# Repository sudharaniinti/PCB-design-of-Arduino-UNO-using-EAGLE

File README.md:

# PCB-design-of-Arduino-UNO-using-EAGLE
PCB (Printed Circuit Board) designing is the process of creating the layout and design of a printed circuit board used to connect electronic components. I designed my first PCB using EAGLE Software! I designed an Arduino UNO board with basic features, including a Microcontroller module, Power Module, and input/output pins. EAGLE is electronic design automation (EDA) software that lets printed circuit board (PCB) designers seamlessly connect schematic diagrams, component placement, PCB routing and comprehensive library content.  EAGLE stands for Easily Applicable Graphical Layout Editor 

This repository contains the following:

1. Eagle schematic file

2. Eagle board file

3. BOM(Bill of Materials)

4. Gerbers

5. PDFs of the schematic

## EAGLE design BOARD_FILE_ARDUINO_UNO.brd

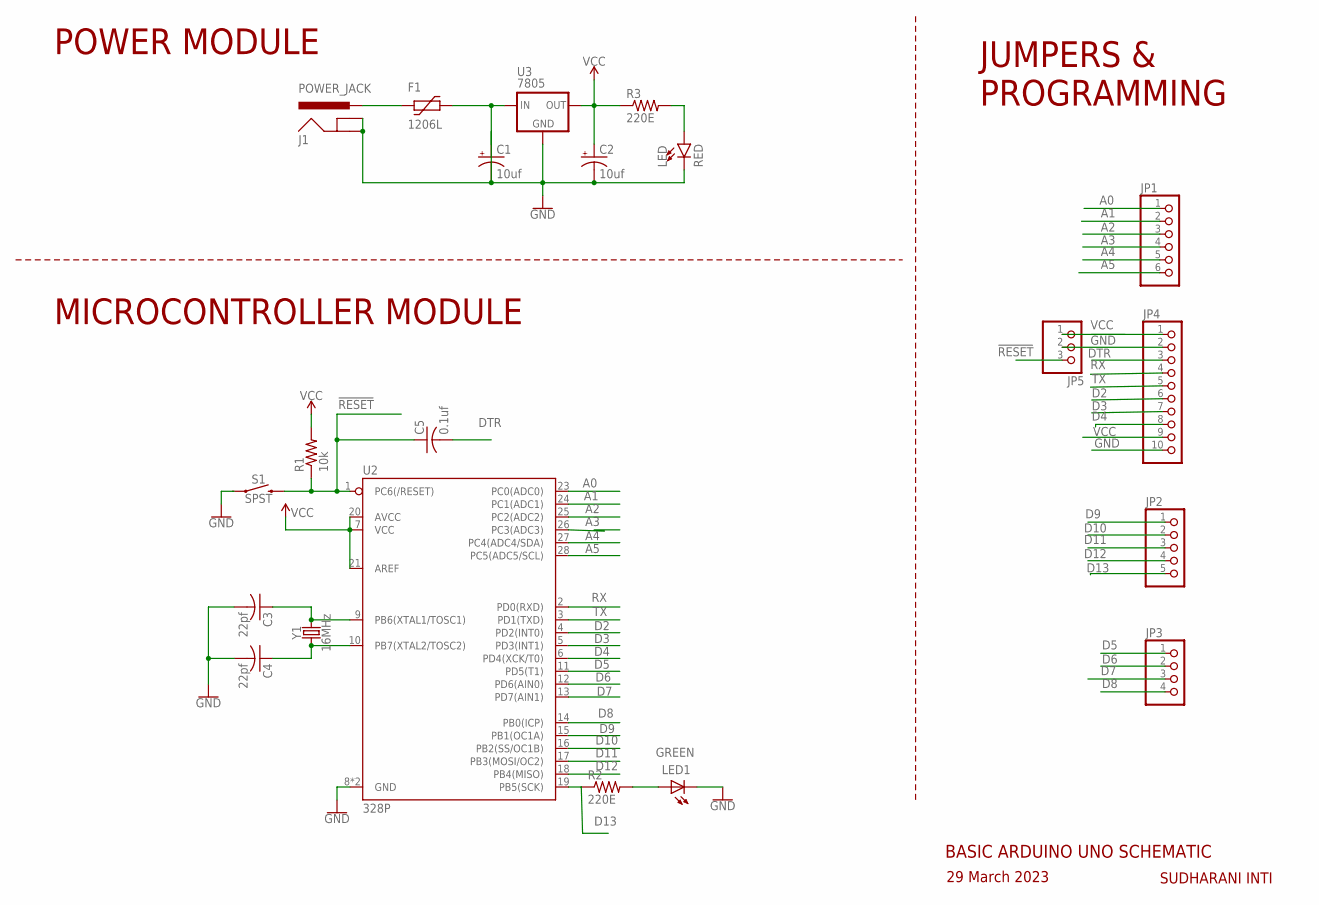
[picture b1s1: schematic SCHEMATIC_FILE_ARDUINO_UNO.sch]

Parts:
C1, C2: 10uf; E2,5-6E
C3, C4: 22pf; C025-024X044
C5: 0.1uf; C025-024X044
F1: 1206L
J1: POWER_JACK; POWER_JACK_PTH
JP1: PINHD-1X6; 1X06
JP2: PINHD-1X5; 1X05
JP3: PINHD-1X4; 1X04
JP4: PINHD-1X10; 1X10
JP5: PINHD-1X3; 1X03
LED: RED; LED_3MM
LED1: GREEN; LED3MM
R1: 10k; 0204/7
R2, R3: 220E; 0204/7
S1: SPST; TACTILE_SWITCH_PTH_6.0MM
U2: 328P; DIP28
U3: 7805; 78XXS
Y1: 16MHz; HC49US

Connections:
!RESET: C5.1, JP5.3, R1.1, S1.3 (2), U2.1 (PC6(/RESET))
A0: JP1.1, U2.23 (PC0(ADC0))
A1: JP1.2, U2.24 (PC1(ADC1))
A2: JP1.3, U2.25 (PC2(ADC2))
A3: JP1.4, U2.26 (PC3(ADC3))
A4: JP1.5, U2.27 (PC4(ADC4/SDA))
A5: JP1.6, U2.28 (PC5(ADC5/SCL))
D2: JP4.6, U2.4 (PD2(INT0))
D3: JP4.7, U2.5 (PD3(INT1))
D4: JP4.8, U2.6 (PD4(XCK/T0))
D5: JP3.1, U2.11 (PD5(T1))
D6: JP3.2, U2.12 (PD6(AIN0))
D7: JP3.3, U2.13 (PD7(AIN1))
D8: JP3.4, U2.14 (PB0(ICP))
D9: JP2.1, U2.15 (PB1(OC1A))
D10: JP2.2, U2.16 (PB2(SS/OC1B))
D11: JP2.3, U2.17 (PB3(MOSI/OC2))
D12: JP2.4, U2.18 (PB4(MISO))
D13: JP2.5, R2.1, U2.19 (PB5(SCK))
DTR: C5.2, JP4.3
GND: C1.-, C2.-, C3.2, C4.2, J1.GND, J1.GNDBREAK, JP4.2, JP4.10, JP5.2, LED.K (C), LED1.K (C), S1.1, U2.8 (GND), U2.22 (GND), U3.GND
unnamed: C1.+, F1.P$2 (2), U3.IN
unnamed: C3.1, U2.9 (PB6(XTAL1/TOSC1)), Y1.2
unnamed: C4.1, U2.10 (PB7(XTAL2/TOSC2)), Y1.1
unnamed: LED.A, R3.2
unnamed: LED1.A, R2.2
unnamed: F1.P$1 (1), J1.PWR
RX: JP4.4, U2.2 (PD0(RXD))
TX: JP4.5, U2.3 (PD1(TXD))
VCC: C2.+, JP4.1, JP4.9, JP5.1, R1.2, R3.1, U2.7 (VCC), U2.20 (AVCC), U2.21 (AREF), U3.OUT

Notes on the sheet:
POWER MODULE
MICROCONTROLLER MODULE
JUMPERS & PROGRAMMING
BASIC ARDUINO UNO SCHEMATIC
SUDHARANI INTI
29 March 2023

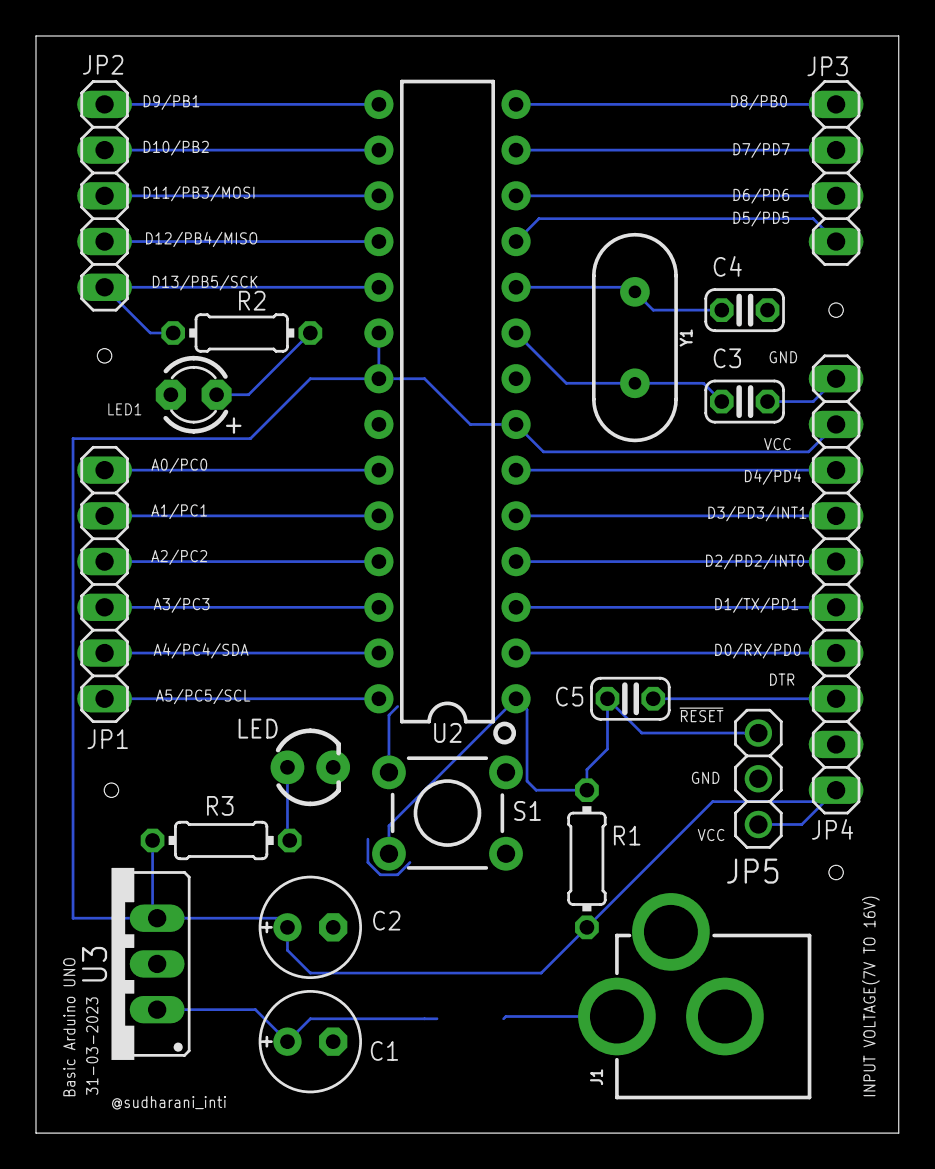
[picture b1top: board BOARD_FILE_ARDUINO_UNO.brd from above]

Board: 2 copper layers, 47.9 x 61.0 mm, 21 parts (1 on the bottom side), 30 nets.

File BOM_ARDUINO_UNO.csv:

"Qty";"Value";"Device";"Package";"Parts";"Description";"";
"1";"";"PINHD-1X10";"1X10";"JP4";"PIN HEADER";"";
"1";"";"PINHD-1X3";"1X03";"JP5";"PIN HEADER";"";
"1";"";"PINHD-1X4";"1X04";"JP3";"PIN HEADER";"";
"1";"";"PINHD-1X5";"1X05";"JP2";"PIN HEADER";"";
"1";"";"PINHD-1X6";"1X06";"JP1";"PIN HEADER";"";
"1";"0.1uf";"C-US025-024X044";"C025-024X044";"C5";"CAPACITOR, American symbol";"";
"1";"10k";"R-US_0204/7";"0204/7";"R1";"RESISTOR, American symbol";"";
"2";"10uf";"CPOL-USE2,5-6E";"E2,5-6E";"C1, C2";"POLARIZED CAPACITOR, American symbol";"";
"1";"1206L";"1206L";"1206L";"F1";"";"";
"1";"16MHz";"CRYSTAL-16MHZPTH-HC49US";"HC49US";"Y1";"16MHz Crystal";"";
"2";"220E";"R-US_0204/7";"0204/7";"R2, R3";"RESISTOR, American symbol";"";
"2";"22pf";"C-US025-024X044";"C025-024X044";"C3, C4";"CAPACITOR, American symbol";"";
"1";"328P";"ATMEGA328P_PDIP";"DIP28";"U2";"Atmel 328P";"";
"1";"7805";"78XXS";"78XXS";"U3";"VOLTAGE REGULATOR";"";
"1";"GREEN";"LED3MM";"LED3MM";"LED1";"LED";"";
"1";"POWER_JACK";"POWER_JACK";"POWER_JACK_PTH";"J1";"Power Jack Connector";"";
"1";"RED";"LED3MM";"LED_3MM";"LED";"LED (Generic)";"";
"1";"SPST";"MOMENTARY-SWITCH-SPST-PTH-6.0MM";"TACTILE_SWITCH_PTH_6.0MM";"S1";"Momentary Switch (Pushbutton) - SPST";"";

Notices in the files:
parts and their libraries:
SparkFun-Connectors: Licensing: Creative Commons ShareAlike 4.0 International - https://creativecommons.org/licenses/by-sa/4.0
